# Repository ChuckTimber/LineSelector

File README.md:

# LineSelector

[ラインセレクタ - DIY Fx and Synthesizer](https://scrapbox.io/diyfx/%E3%83%A9%E3%82%A4%E3%83%B3%E3%82%BB%E3%83%AC%E3%82%AF%E3%82%BF)

## 仕様
- 基本仕様は A-B-Thru
- I/O は，Input / Output / SendA-ReturnA / SendB-ReturnB / TunerOut
- ２ボタン（A/B切替ボタン と Thru/FX切替ボタン）コントロール
- A/B切り替えボタンで SendA-ReturnA / SendB-ReturnB を切り替え
- Thru/FX ボタン長押しで Tunerモード（本線系はミュートしてチューナにのみ信号を流す）．Thru/FXボタンかA/Bボタンで復帰．
- なお切り替え制御はワンチップマイコン使用

## 回路図

- [version 1.0](Line_Selector_v1p0.pdf) 一部間違いあり，基板パターンを改修した上で動作実績あり
- [version 1.1](Line_Selector_v1p1.pdf) v.1.1を修正したもの．ただし基板は製作しておらず未検証

## 基板修正図

- [Patch 1.0 to 1.1](Patch_v1p0_to_v1p1.pdf) verion 1.0 の基板に対するパッチ情報（基板カットとジャンパ線）

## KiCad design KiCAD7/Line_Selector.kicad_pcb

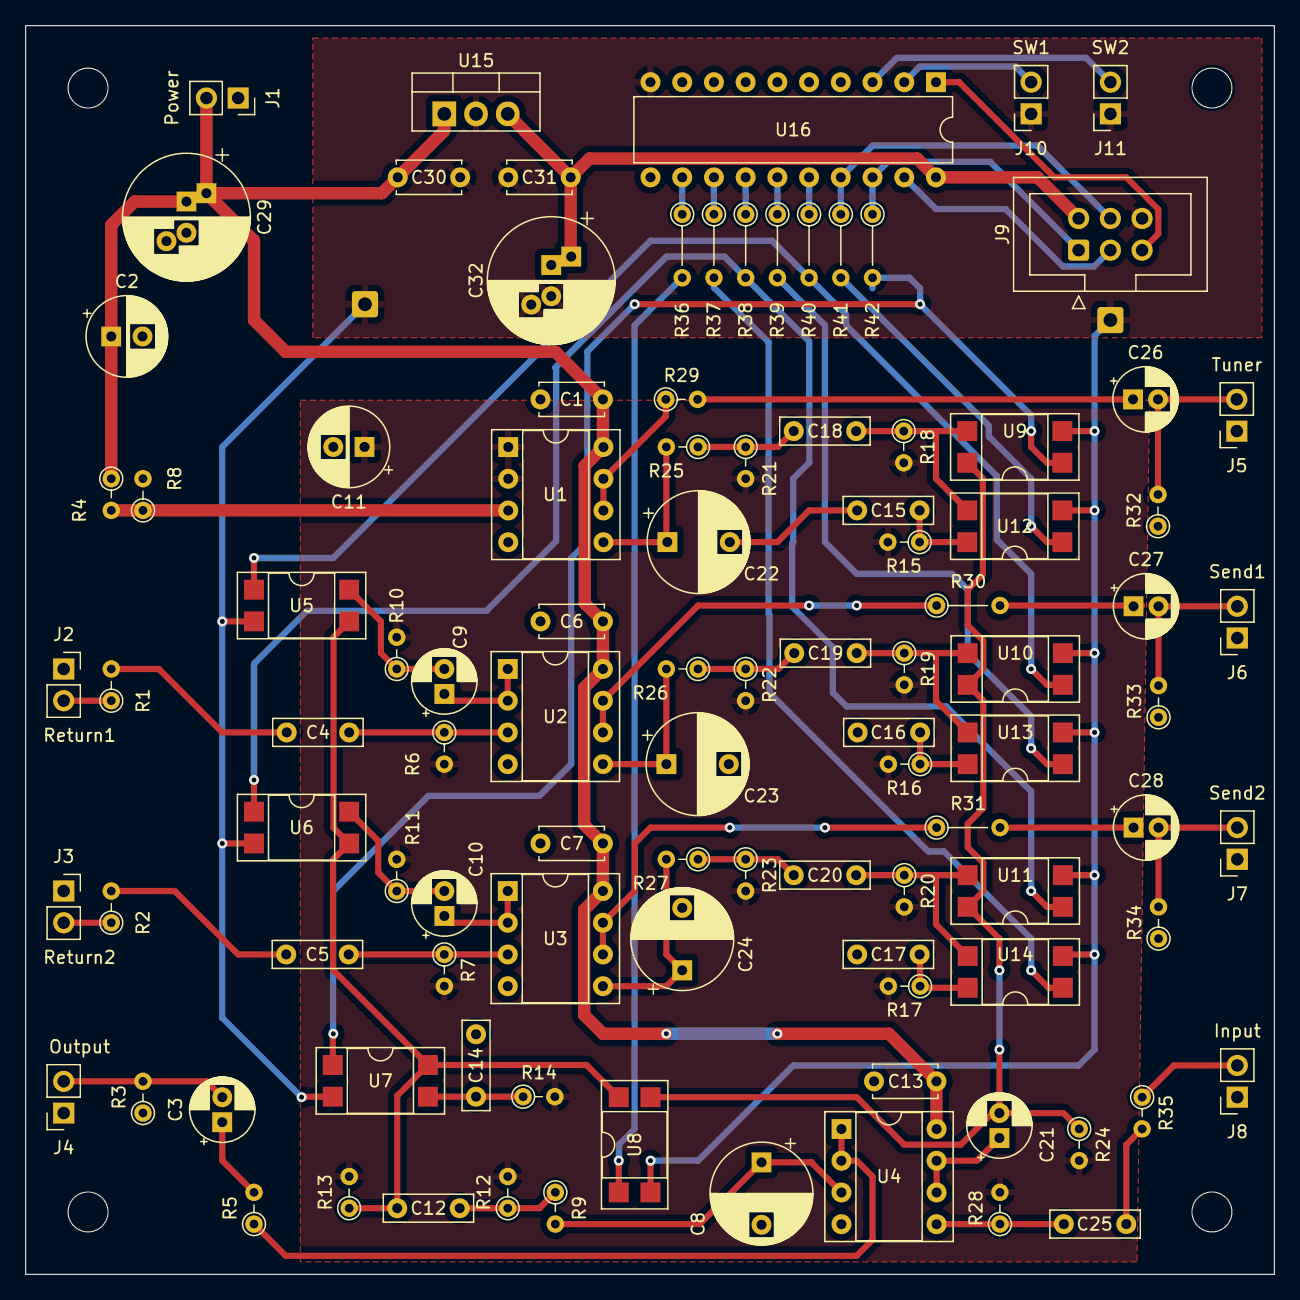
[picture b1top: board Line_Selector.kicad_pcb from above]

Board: 2 copper layers, 100.0 x 100.0 mm, 107 parts (0 on the bottom side), 67 nets.

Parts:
C1, C6, C7, C13, C30, C31: 100n; C_Disc_D5.0mm_W2.5mm_P5.00mm
C2, C11: 100u/16V; CP_Radial_D6.3mm_P2.50mm
C3, C9, C10, C21, C26, C27, C28: 1u/50V; CP_Radial_D5.0mm_P2.00mm
C4, C5, C12, C14, C15, C16, C17, C18, C19, C20, C25: 47n; C_Rect_L7.0mm_W2.0mm_P5.00mm
C8, C22, C23, C24: 470p; CP_Radial_D8.0mm_P5.00mm
C29, C32: 220u/35V; CP_Radial_D10.0mm_P2.50mm_P5.00mm
H1, H2, H3, H4: MountingHole; MountingHole_3.2mm_M3
J1: Power; PinSocket_1x02_P2.54mm_Vertical
J2: Return1; PinSocket_1x02_P2.54mm_Vertical
J3: Return2; PinSocket_1x02_P2.54mm_Vertical
J4: Output; PinSocket_1x02_P2.54mm_Vertical
J5: Tuner; PinSocket_1x02_P2.54mm_Vertical
J6: Send1; PinSocket_1x02_P2.54mm_Vertical
J7: Send2; PinSocket_1x02_P2.54mm_Vertical
J8: Input; PinSocket_1x02_P2.54mm_Vertical
J9: AVR-ISP-6; IDC-Header_2x03_P2.54mm_Vertical
J10: SW1; PinSocket_1x02_P2.54mm_Vertical
J11: SW2; PinSocket_1x02_P2.54mm_Vertical
J12, J13: Conn_01x01_Pin; SolderWire-0.5sqmm_1x01_D0.9mm_OD2.1mm
R1, R2, R35: 10k; R_Axial_DIN0204_L3.6mm_D1.6mm_P2.54mm_Vertical
R3, R32, R33, R34: 100k; R_Axial_DIN0204_L3.6mm_D1.6mm_P2.54mm_Vertical
R4, R8: 33k; R_Axial_DIN0204_L3.6mm_D1.6mm_P2.54mm_Vertical
R5, R9, R25, R26, R27, R29: 1k; R_Axial_DIN0204_L3.6mm_D1.6mm_P2.54mm_Vertical
R6, R7, R10, R11, R12, R13, R14, R15, R16, R17, R18, R19, R20, R21, R22, R23, R24, R28: 1M; R_Axial_DIN0204_L3.6mm_D1.6mm_P2.54mm_Vertical
R30, R31, R36, R37, R38, R39, R40, R41, R42: 1k; R_Axial_DIN0204_L3.6mm_D1.6mm_P5.08mm_Vertical
U1, U2, U3, U4: NJM4558; DIP-8_W7.62mm_Socket
U5, U6, U7, U8, U9, U10, U11, U12, U13, U14: TLP241A; DIP-4_W7.62mm_SMDSocket_SmallPads
U15: LM78M05_TO220; TO-220-3_Vertical
U16: ATtiny2313-20P; DIP-20_W7.62mm

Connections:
+5V: C31.1, C32.1, J9.2 (VCC), U15.3 (VO), U16.20 (VCC)
+9V: C1.1, C2.1, C6.1, C7.1, C13.1, C29.1, C30.1, J1.2, R4.1, U1.8 (V+), U2.8 (V+), U3.8 (V+), U4.8 (V+), U15.1 (VI)
GND: C1.2, C2.2, C6.2, C7.2, C8.2, C11.2, C13.2, C14.2, C15.2, C16.2, C17.2, C22.2, C23.2, C24.2, C29.2, J1.1, J2.1, J3.1, J4.1, J5.1, J6.1, J7.1, J8.1, R3.1, R8.2, R32.1, R33.1, R34.1, U1.4 (V-), U2.4 (V-), U3.4 (V-), U4.4 (V-)
GNDD: C30.2, C31.2, C32.2, J9.6 (GND), J10.1, J11.1, J12.1, J13.1, U5.2, U6.2, U7.2, U8.2, U9.2, U10.2, U11.2, U12.2, U13.2, U14.2, U15.2 (GND), U16.10 (GND)
unnamed: C3.1, R5.2
unnamed: C4.1, R1.2
unnamed: C5.1, R2.2
unnamed: C9.2, R10.1, U5.4
unnamed: C10.2, R11.1, U6.4
unnamed: C12.1, R13.1, U5.3, U6.3, U7.4, U8.4
unnamed: C12.2, R9.1, R12.1
unnamed: C14.1, R14.1, U7.3
unnamed: C15.1, R15.1, U12.4
unnamed: C16.1, R16.1, U13.4
unnamed: C17.1, R17.1, U14.4
unnamed: C18.1, R18.1, U9.3, U12.3
unnamed: C18.2, R21.1, R25.1
unnamed: C19.1, R19.1, U10.3, U13.3
unnamed: C19.2, R22.1, R26.1
unnamed: C20.1, R20.1, U11.3, U14.3
unnamed: C20.2, R23.1, R27.1
unnamed: C21.2, R24.1, U8.3, U9.4, U10.4, U11.4
unnamed: C25.1, R35.2
unnamed: C26.1, R29.2
unnamed: C27.1, R30.2
unnamed: C28.1, R31.2
unnamed: J2.2, R1.1
unnamed: J3.2, R2.1
unnamed: C3.2, J4.2, R3.2
unnamed: C26.2, J5.2, R32.2
unnamed: C27.2, J6.2, R33.2
unnamed: C28.2, J7.2, R34.2
unnamed: J8.2, R35.1
unnamed: J9.1 (MISO), R42.1, U16.18 (PB6)
unnamed: J9.4 (MOSI), R41.1, U16.17 (PB5)
unnamed: J9.3 (SCK), U16.19 (PB7)
unnamed: J9.5 (~RST), U16.1 (PA2/~RESET)
unnamed: J10.2, U16.2 (PD0)
unnamed: J11.2, U16.3 (PD1)
unnamed: R4.2, R8.1, U1.3 (+)
unnamed: C22.1, R25.2, U1.5 (+)
unnamed: R29.1, U1.6 (-), U1.7
unnamed: C4.2, R6.1, U2.3 (+)
unnamed: C9.1, U2.1, U2.2 (-)
unnamed: C23.1, R26.2, U2.5 (+)
unnamed: R30.1, U2.6 (-), U2.7
unnamed: C5.2, R7.1, U3.3 (+)
unnamed: C10.1, U3.1, U3.2 (-)
unnamed: C24.1, R27.2, U3.5 (+)
unnamed: R31.1, U3.6 (-), U3.7
unnamed: C8.1, R9.2, U4.3 (+)
unnamed: R5.1, U4.1, U4.2 (-)
unnamed: C25.2, R28.1, U4.5 (+)
unnamed: C21.1, U4.6 (-), U4.7
unnamed: R36.1, U16.12 (PB0)
unnamed: R37.1, U16.13 (PB1)
unnamed: R38.1, U16.14 (PB2)
unnamed: R39.1, U16.15 (PB3)
unnamed: R40.1, U16.16 (PB4)
S1: R36.2, U8.1
S4: R41.2, U12.1
S7: R39.2, U13.1
S10: R37.2, U14.1
S23: R42.2, U7.1, U9.1
S56: R40.2, U5.1, U10.1
S89: R38.2, U6.1, U11.1
VCOM: C11.1, R6.2, R7.2, R10.2, R11.2, R12.2, R13.2, R14.2, R15.2, R16.2, R17.2, R18.2, R19.2, R20.2, R21.2, R22.2, R23.2, R24.2, R28.2, U1.1, U1.2 (-)

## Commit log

2023-12-12 Add schematic PDF
2023-12-12 Added KiCAD portion
2023-12-12 Added Software portion
2023-12-12 README.md modified
2023-12-12 modified README.md
2024-01-08 Added the pcb patch information
2026-01-19 Create LICENSE.md
    Added LICENSE.md
